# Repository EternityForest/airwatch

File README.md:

# AirWatch: ESP8266 I2C/ADC/Battery board

#AS IS!!!!!
I've changed some stuff since actually building these. I'll write some proper docs eventually I suppose.
Mostly just gettingthis under VC.

## Features/Hacks used

* Somethinng is wrong with the 0805 footprints. The
* There's a ton of voltage  drop on the way to the battery. 
* It might only charge to 50% from 5v. Good enough, they don't like full charge anyway.
* WiFi Is Fussy! Or maybe it isn't? I'm testing with unfinished code.
* Totally untested fancy easy to solder bigger 0805 pads!

* You can't use the TX pin, it controls the battery charger
* Ok, maybe the world won't end if you send some stuff anyway?
* You can controll the charger!
* 5v-24v input.
* No onboard programming
* A button! It conflicts with the RX pin!
* A power switch! That actually disconnecxts the battery!
* A reliance on the load dump protectionof the LDO
* ^ to save it from the tiny reverse current in battery mode when filling the input cap
* An ADC(ADS1015 at 0x49, not the adafruit lib default)

* read the schematic
* a transistor as a standin for a reg I didn't have a footprint for
* The reg will probably overheat if you use it from more than 7v or so, unless you're always in sleep mode.
* Will probably not work at all if you use a cheaper LDO
* seriously read it

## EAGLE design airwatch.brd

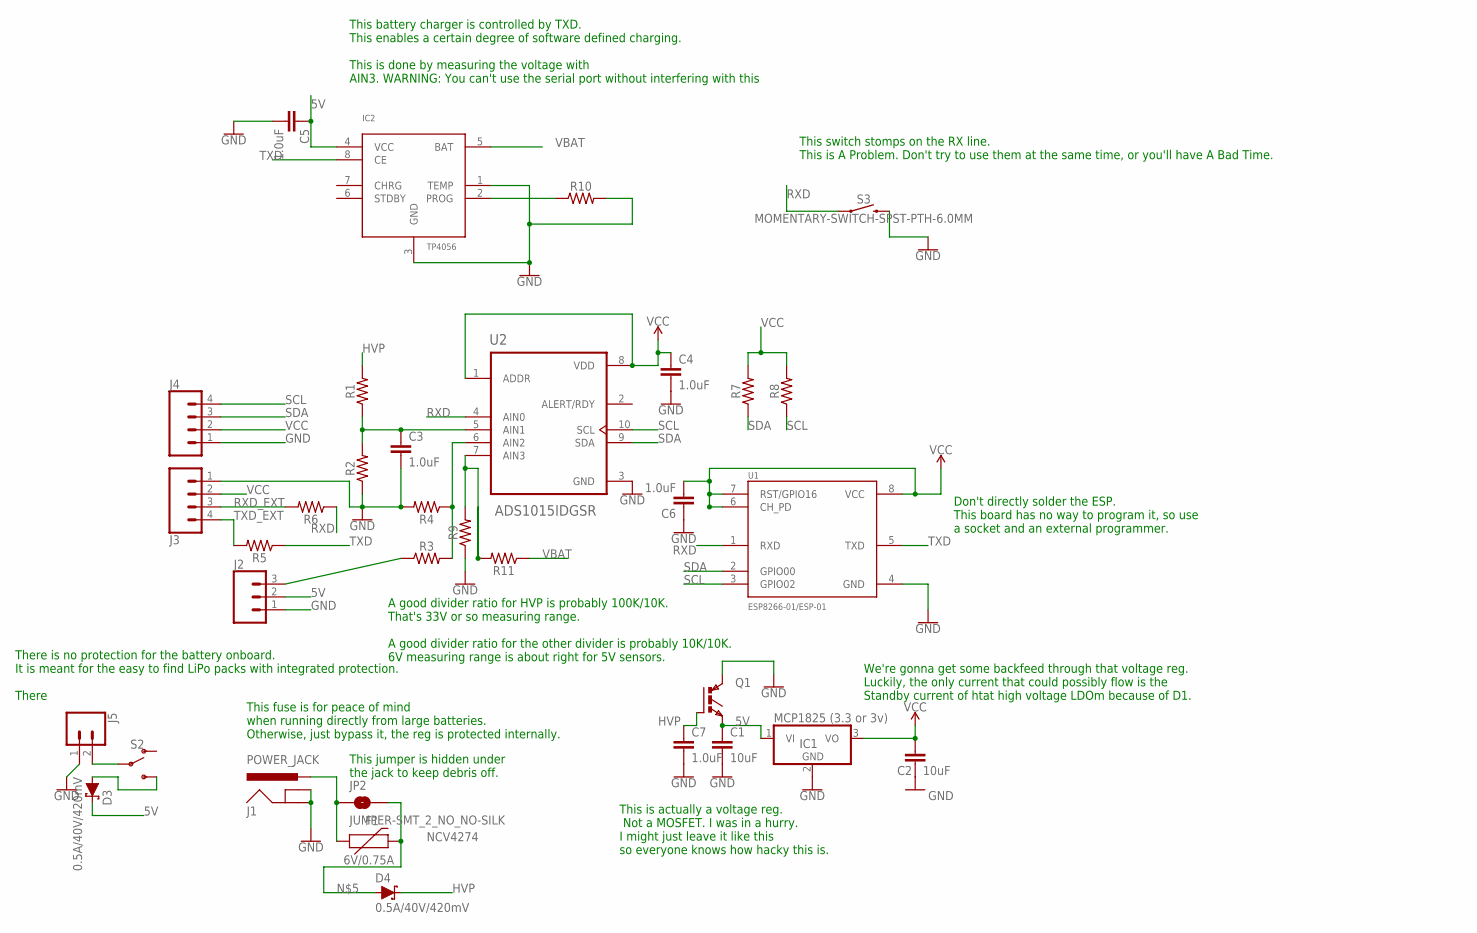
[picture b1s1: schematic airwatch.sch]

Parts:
C1, C2: 10uF; 0805
C3, C4, C5, C7: 1.0uF; 0805-EZ
C6: 1.0uF; 1206-EZ
D3, D4: 0.5A/40V/420mV; SOD-323
F1: 6V/0.75A; 1206
IC1: MCP1825 (3.3 or 3v); SOT223
IC2: TP4056; SOP-8
J1: POWER_JACK; POWER_JACK_PTH
J2: CONN_03JST-PTH-VERT; JST-3-PTH-VERT
J3, J4: CONN_04JST-PTH-VERT; JST-4-PTH-VERT
J5: CONN_02JST-PTH-2; JST-2-PTH
JP2: JUMPER-SMT_2_NO_NO-SILK; SMT-JUMPER_2_NO_NO-SILK
Q1: NCV4274; TO252_STM
R1, R2, R3, R4, R5, R6, R7, R8, R9, R10, R11: 0805-EZ
S2: SWITCH-SPDT-PTH-11.6X4.0MM-LOCK; SWITCH_SPDT_PTH_11.6X4.0MM_LOCK
S3: MOMENTARY-SWITCH-SPST-PTH-6.0MM; TACTILE_SWITCH_PTH_6.0MM
U1: ESP8266-01/ESP-01; XCVR_ESP8266-01/ESP-01
U2: ADS1015IDGSR; SOP50P490X110-10N

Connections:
5V: C1.1, C5.1, D3.C, IC1.1 (VI), IC2.4 (VCC), J2.2, Q1.3 (E)
GND: C1.2, C2.2, C3.2, C4.2, C5.2, C6.1, C7.2, IC1.2 (GND), IC2.1 (TEMP), IC2.3 (GND), J1.GND, J1.GNDBREAK, J2.1, J3.1, J4.1, J5.1, Q1.2 (C), R2.1, R4.2, R9.1, R10.2, S3.3 (2), U1.4 (GND), U2.3 (GND)
HVP: C7.1, D4.C, Q1.1 (G), R1.2
unnamed: J2.3, R3.1
unnamed: R3.2, R4.1, U2.6 (AIN2)
unnamed: R9.2, R11.2, U2.7 (AIN3)
unnamed: D4.A, F1.2, JP2.2
unnamed: C3.1, R1.1, R2.2, U2.5 (AIN1)
unnamed: F1.1, J1.PWR, JP2.1
unnamed: J5.2, S2.2
unnamed: IC2.2 (PROG), R10.1
RXD: R6.1, S3.1, U1.1 (RXD), U2.4 (AIN0)
RXD_EXT: J3.3, R6.2
SCL: J4.4, R8.1, U1.3 (GPIO02), U2.10 (SCL)
SDA: J4.3, R7.1, U1.2 (GPIO00), U2.9 (SDA)
TXD: IC2.8 (CE), R5.1, U1.5 (TXD)
TXD_EXT: J3.4, R5.2
VBAT: D3.A, IC2.5 (BAT), R11.1, S2.3 (S)
VCC: C2.1, C4.1, C6.2, IC1.3 (VO), J3.2, J4.2, R7.2, R8.2, U1.6 (CH_PD), U1.7 (RST/GPIO16), U1.8 (VCC), U2.1 (ADDR), U2.8 (VDD)

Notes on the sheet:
This is actually a voltage reg. Not a MOSFET. I was in a hurry. I might just leave it like this so everyone knows how hacky this is.
Don't directly solder the ESP. This board has no way to program it, so use a socket and an external programmer.
This switch stomps on the RX line. This is A Problem. Don't try to use them at the same time, or you'll have A Bad Time.
A good divider ratio for HVP is probably 100K/10K. That's 33V or so measuring range. A good divider ratio for the other divider is probably 10K/10K. 6V measuring range is about right for 5V sensors.
We're gonna get some backfeed through that voltage reg. Luckily, the only current that could possibly flow is the Standby current of htat high voltage LDOm because of D1.
This fuse is for peace of mind when running directly from large batteries. Otherwise, just bypass it, the reg is protected internally.
This jumper is hidden under the jack to keep debris off.
This battery charger is controlled by TXD. This enables a certain degree of software defined charging. This is done by measuring the voltage with AIN3. WARNING: You can't use the serial port without interfering with this
There is no protection for the battery onboard. It is meant for the easy to find LiPo packs with integrated protection. There

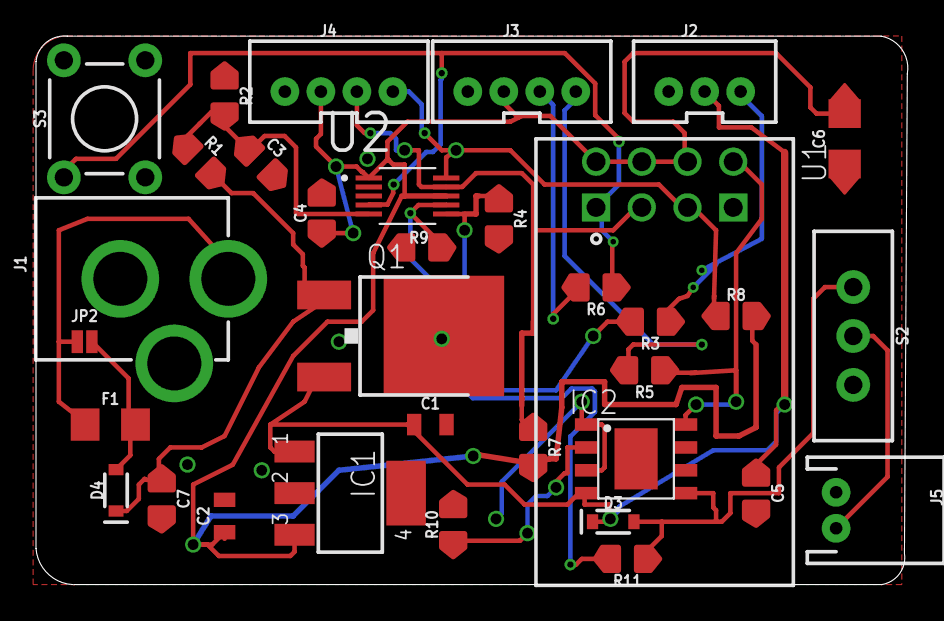
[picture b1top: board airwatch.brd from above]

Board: 2 copper layers, 48.4 x 30.5 mm, 34 parts (0 on the bottom side), 19 nets.

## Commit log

2019-01-25 First super hacky barely tested commit
2019-01-25 Soldermask for the 0805-ez pads. Totally untested, might even revert.

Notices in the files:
parts and their libraries:
SparkFun-Connectors: Licensing: Creative Commons ShareAlike 4.0 International - https://creativecommons.org/licenses/by-sa/4.0
